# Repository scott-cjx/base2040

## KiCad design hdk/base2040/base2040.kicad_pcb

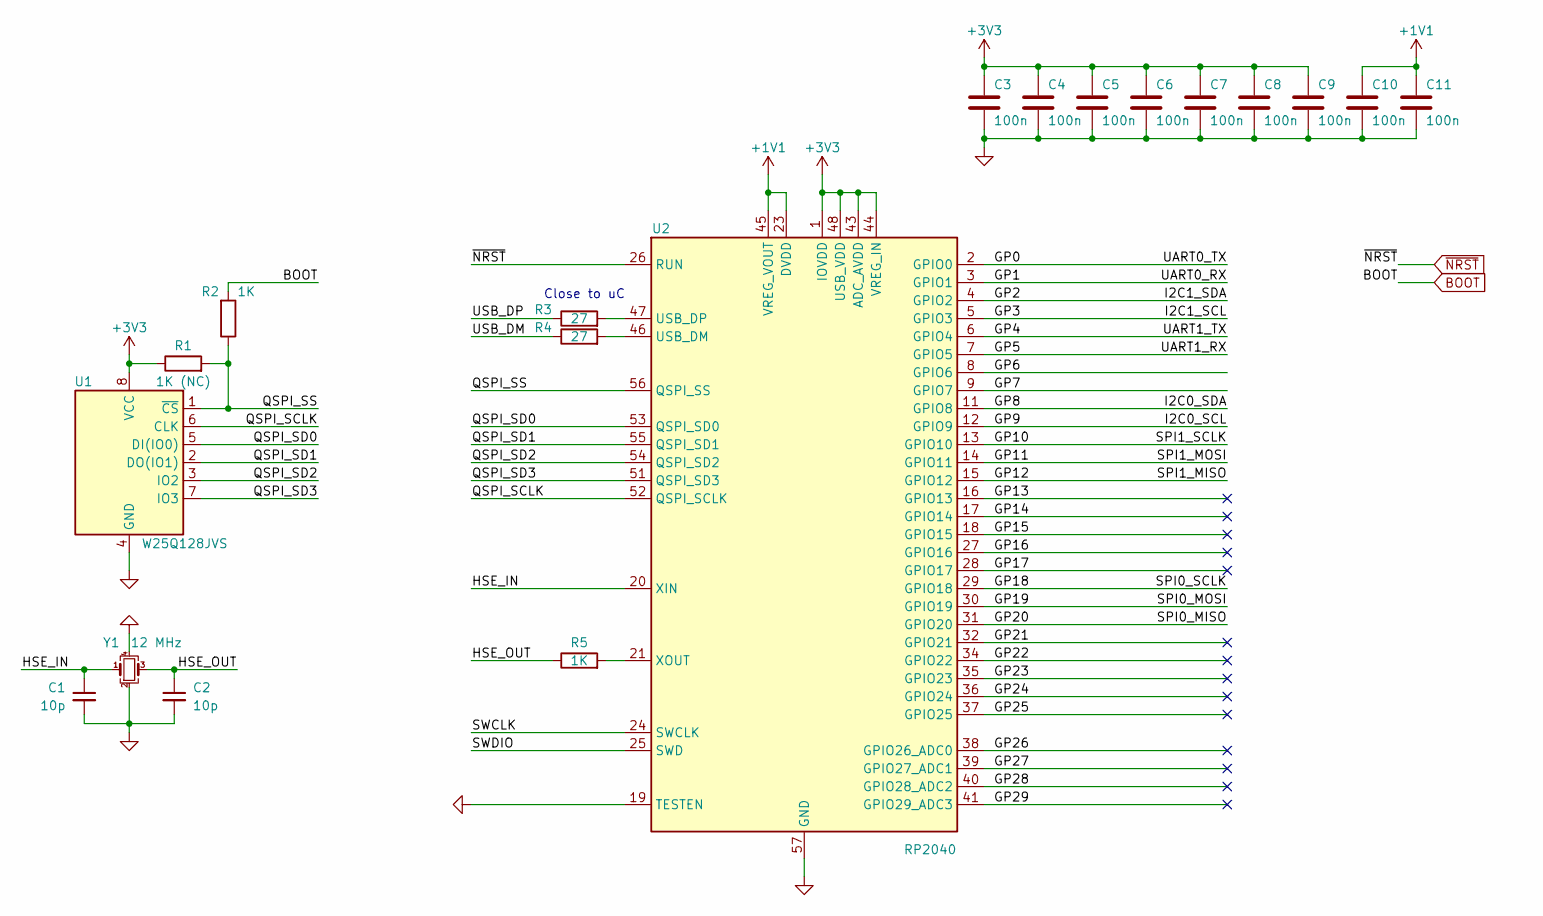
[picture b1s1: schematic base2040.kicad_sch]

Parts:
C1, C2: 10p; C_0402_1005Metric
C3, C4, C5, C6, C7, C8, C9, C10, C11: 100n; C_0402_1005Metric
R1: 1K (NC); R_0402_1005Metric
R2, R5: 1K; R_0402_1005Metric
R3, R4: 27; R_0402_1005Metric
U1: W25Q128JVS; SOIC-8_5.23x5.23mm_P1.27mm
U2: RP2040; QFN-56-1EP_7x7mm_P0.4mm_EP3.2x3.2mm
Y1: 12 MHz; Crystal_SMD_3225-4Pin_3.2x2.5mm

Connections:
+1V1: C10.1, C11.1, U2.23 (DVDD), U2.45 (VREG_VOUT), U2.50 (DVDD)
+3V3: C3.1, C4.1, C5.1, C6.1, C7.1, C8.1, C9.1, R1.1, U1.8 (VCC), U2.1 (IOVDD), U2.10 (IOVDD), U2.22 (IOVDD), U2.33 (IOVDD), U2.42 (IOVDD), U2.43 (ADC_AVDD), U2.44 (VREG_IN), U2.48 (USB_VDD), U2.49 (IOVDD)
/GP0: U2.2 (GPIO0)
/GP1: U2.3 (GPIO1)
/GP2: U2.4 (GPIO2)
/GP3: U2.5 (GPIO3)
/GP4: U2.6 (GPIO4)
/GP5: U2.7 (GPIO5)
/GP6: U2.8 (GPIO6)
/GP7: U2.9 (GPIO7)
/GP8: U2.11 (GPIO8)
/GP9: U2.12 (GPIO9)
/GP10: U2.13 (GPIO10)
/GP11: U2.14 (GPIO11)
/GP12: U2.15 (GPIO12)
/GP13: U2.16 (GPIO13)
/GP14: U2.17 (GPIO14)
/GP15: U2.18 (GPIO15)
/GP16: U2.27 (GPIO16)
/GP17: U2.28 (GPIO17)
/GP18: U2.29 (GPIO18)
/GP19: U2.30 (GPIO19)
/GP20: U2.31 (GPIO20)
/GP21: U2.32 (GPIO21)
/GP22: U2.34 (GPIO22)
/GP23: U2.35 (GPIO23)
/GP24: U2.36 (GPIO24)
/GP25: U2.37 (GPIO25)
/GP26: U2.38 (GPIO26_ADC0)
/GP27: U2.39 (GPIO27_ADC1)
/GP28: U2.40 (GPIO28_ADC2)
/GP29: U2.41 (GPIO29_ADC3)
/HSE_IN: C1.1, U2.20 (XIN), Y1.1
/HSE_OUT: C2.1, R5.1, Y1.3
/QSPI_SCLK: U1.6 (CLK), U2.52 (QSPI_SCLK)
/QSPI_SD0: U1.5 (DI(IO0)), U2.53 (QSPI_SD0)
/QSPI_SD1: U1.2 (DO(IO1)), U2.55 (QSPI_SD1)
/QSPI_SD2: U1.3 (IO2), U2.54 (QSPI_SD2)
/QSPI_SD3: U1.7 (IO3), U2.51 (QSPI_SD3)
/QSPI_SS: R1.2, R2.1, U1.1 (~CS), U2.56 (QSPI_SS)
/SWCLK: U2.24 (SWCLK)
/SWDIO: U2.25 (SWD)
/USB_DM: R4.1
/USB_DP: R3.1
BOOT: R2.2
GND: C1.2, C2.2, C3.2, C4.2, C5.2, C6.2, C7.2, C8.2, C9.2, C10.2, C11.2, U1.4 (GND), U2.19 (TESTEN), U2.57 (GND), Y1.2, Y1.4
unnamed: R4.2, U2.46 (USB_DM)
unnamed: R3.2, U2.47 (USB_DP)
unnamed: R5.2, U2.21 (XOUT)
~NRST: U2.26 (RUN)

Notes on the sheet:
Close to uC

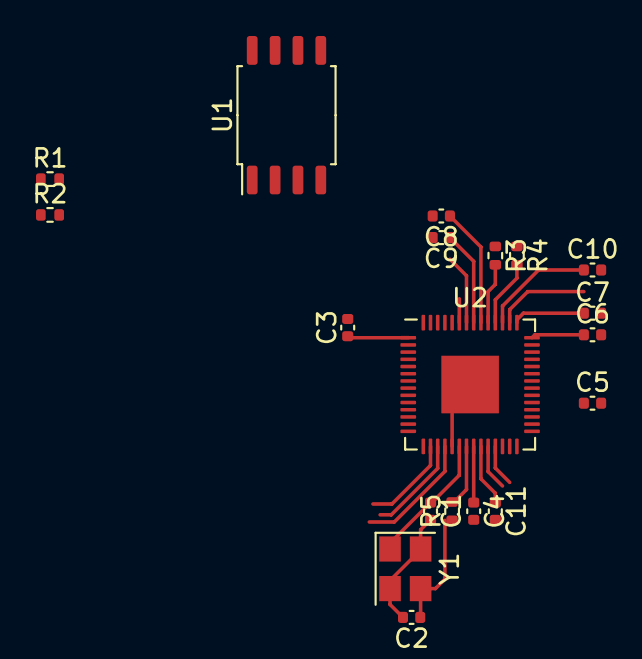
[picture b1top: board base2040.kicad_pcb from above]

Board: 2 copper layers, 19 parts (0 on the bottom side), 14 nets.

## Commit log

2023-12-07 Initialize gh-pages
2023-12-07 Moving files docs/* LICENSE using main
2023-12-07 Deploying to gh-pages from @ scott-cjx/base2040@73432c5583acadc1e27ae7490db10278b0c43b01 🚀
2023-12-07 added base
2023-12-07 Deploying to gh-pages from @ scott-cjx/base2040@a167acbafcaeaffffd14faa3ac40557649693f50 🚀
